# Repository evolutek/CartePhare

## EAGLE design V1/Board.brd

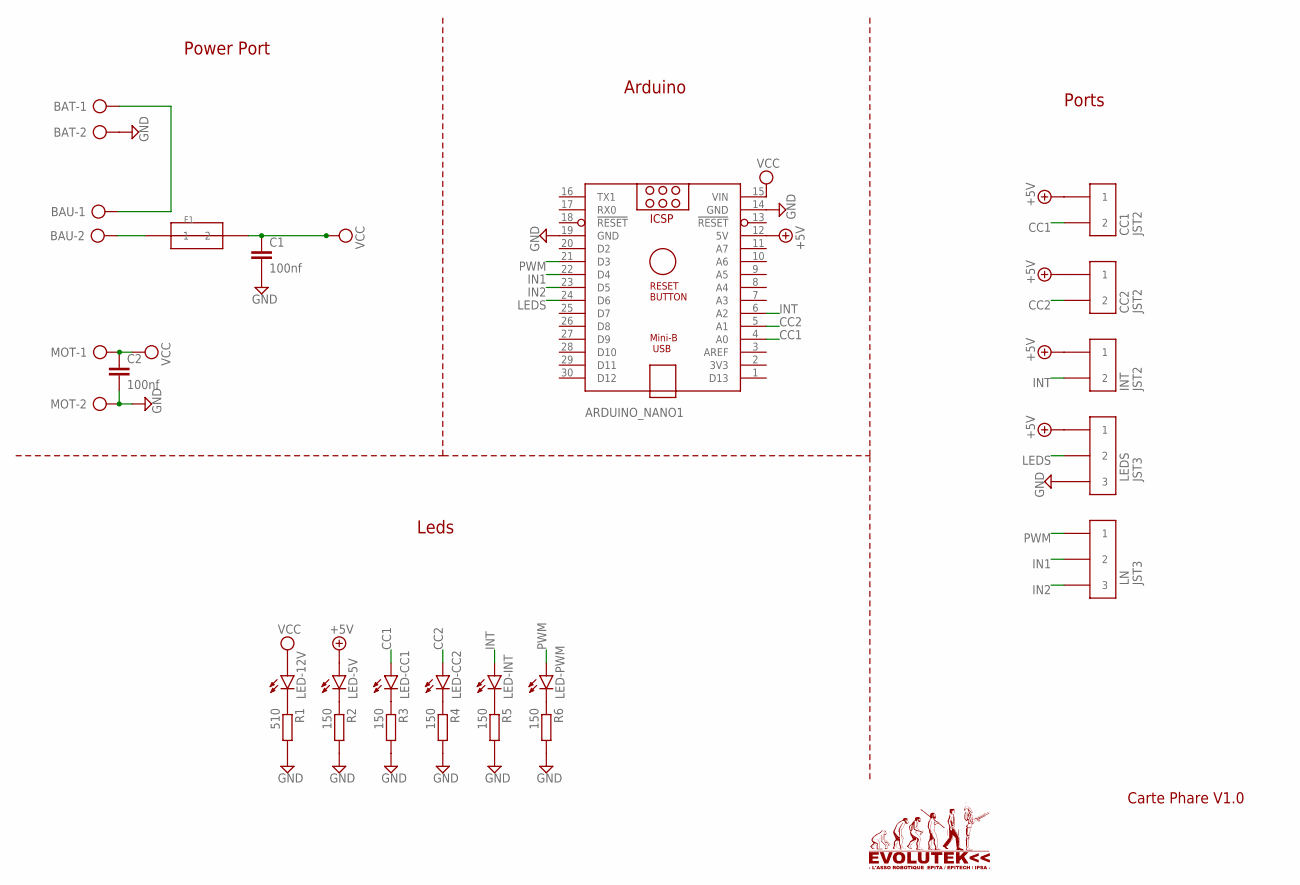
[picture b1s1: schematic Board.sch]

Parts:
ARDUINO_NANO1: ARDUINO_NANO
BAT: AK500/2
BAU: AK500/2
C1, C2: 100nf; C0603
CC1, CC2: JST2; B02B-PASK
F1: 8040-PORTE-FUSIBLE
INT: JST2; B02B-PASK
LED-5V, LED-12V: LEDCHIP-LED0805; CHIP-LED0805
LED-CC1, LED-CC2: LEDCHIP-LED0805; CHIP-LED0805
LED-INT: LEDCHIP-LED0805; CHIP-LED0805
LED-PWM: LEDCHIP-LED0805; CHIP-LED0805
LEDS: JST3; B03B-PASK
LN: JST3; B03B-PASK
MOT: AK500/2
R1: 510; R0603
R2, R3, R4, R5, R6: 150; R0603

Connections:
+5V: ARDUINO_NANO1.12 (5V), CC1.P$1 (1), CC2.P$1 (1), INT.P$1 (1), LED-5V.A, LEDS.P$1 (1)
CC1: ARDUINO_NANO1.4 (A0), CC1.P$2 (2), LED-CC1.A
CC2: ARDUINO_NANO1.5 (A1), CC2.P$2 (2), LED-CC2.A
GND: ARDUINO_NANO1.14 (GND), ARDUINO_NANO1.19 (GND), BAT.2, C1.2, C2.2, LEDS.P$3 (3), MOT.2, R1.2, R2.2, R3.2, R4.2, R5.2, R6.2
IN1: ARDUINO_NANO1.22 (D4), LN.P$2 (2)
IN2: ARDUINO_NANO1.23 (D5), LN.P$3 (3)
INT: ARDUINO_NANO1.6 (A2), INT.P$2 (2), LED-INT.A
LEDS: ARDUINO_NANO1.24 (D6), LEDS.P$2 (2)
unnamed: BAT.1, BAU.1
unnamed: BAU.2, F1.P$1 (1), F1.P$2 (1)
unnamed: LED-12V.C, R1.1
unnamed: LED-5V.C, R2.1
unnamed: LED-CC1.C, R3.1
unnamed: LED-CC2.C, R4.1
unnamed: LED-INT.C, R5.1
unnamed: LED-PWM.C, R6.1
PWM: ARDUINO_NANO1.21 (D3), LED-PWM.A, LN.P$1 (1)
VCC: ARDUINO_NANO1.15 (VIN), C1.1, C2.1, F1.P$3 (2), F1.P$4 (2), LED-12V.A, MOT.1

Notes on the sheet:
Power Port
Ports
Arduino
Leds
Carte Phare V1.0

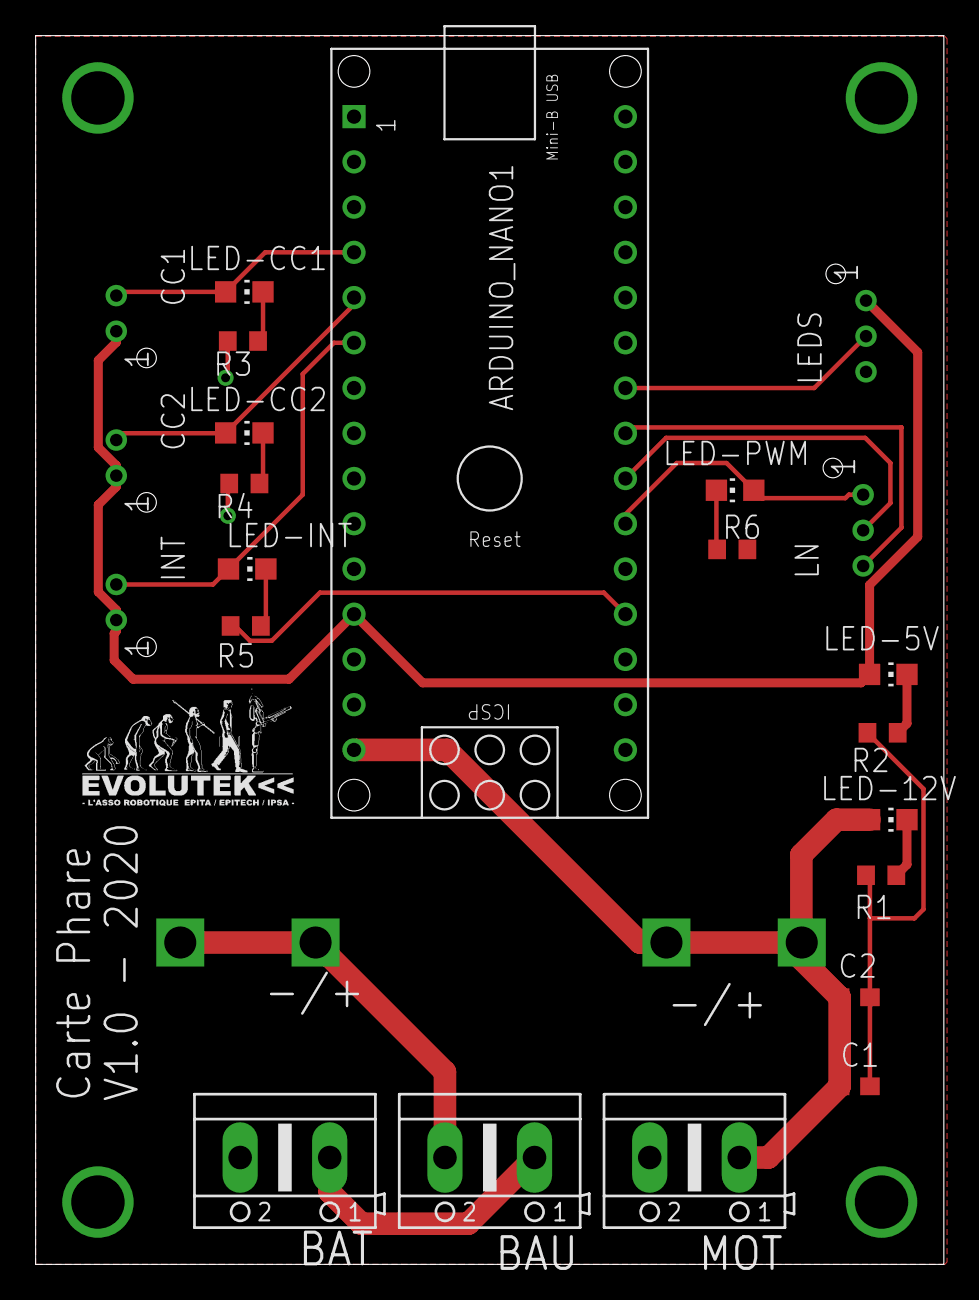
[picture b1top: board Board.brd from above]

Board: 2 copper layers, 51.0 x 69.0 mm, 24 parts (0 on the bottom side), 18 nets.

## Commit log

2020-03-19 Add GITIGNORE
2020-03-19 Add lib
2020-03-19 [V1.0] Add V1.0
2020-05-16 Add code for the board
2020-10-11 Add delay and change color
